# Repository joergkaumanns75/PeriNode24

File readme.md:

# PeriNode24

PeriNode 24 ist ein Zündmodul mit 24 Kanälen und stellt die Standardeinheit dar, welche mehr als einen Zünder pro Kanal auslösen kann.
Ausgelegt ist das Modul für 8 gleichzeitige Zünden mit jeweils 4 in Reihe geschalteten Brückenzündern Typ A.
Wenn nicht alle Kanäle gleichzeitig zünden, kann 6 in Reihe geschaltete Brückenzünder ausgelöst werden, bei guten Bedingungen ggfs. auch mehr.

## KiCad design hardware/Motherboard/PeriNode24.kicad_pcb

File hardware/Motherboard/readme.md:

# PeriNode24 – Motherboard

KiCad-Projekt der PeriNode24-Hauptplatine (ESP32-S3, RFM69HW, 24 Zündkanäle).

| Datei | Inhalt |
|---|---|
| `PeriNode24.kicad_pro` | KiCad-Projekt (hiermit öffnen) |
| `PeriNode24.kicad_sch` | Schaltplan |
| `PeriNode24.kicad_pcb` | Platinenlayout |
| `PeriNode24.pdf` | Schaltplan als PDF |
| `fabrication-toolkit-options.json` | Einstellungen für das Fabrication-Toolkit-Plugin (JLCPCB) |

Verwendet nur KiCad-Standardbibliotheken sowie die Espressif-Bibliothek (Plugin- und Content-Manager).
Lokale Dateien wie `*.kicad_prl`, `fp-info-cache`, Backups und Freerouting-Dateien werden über `hardware/.gitignore` ausgeschlossen.

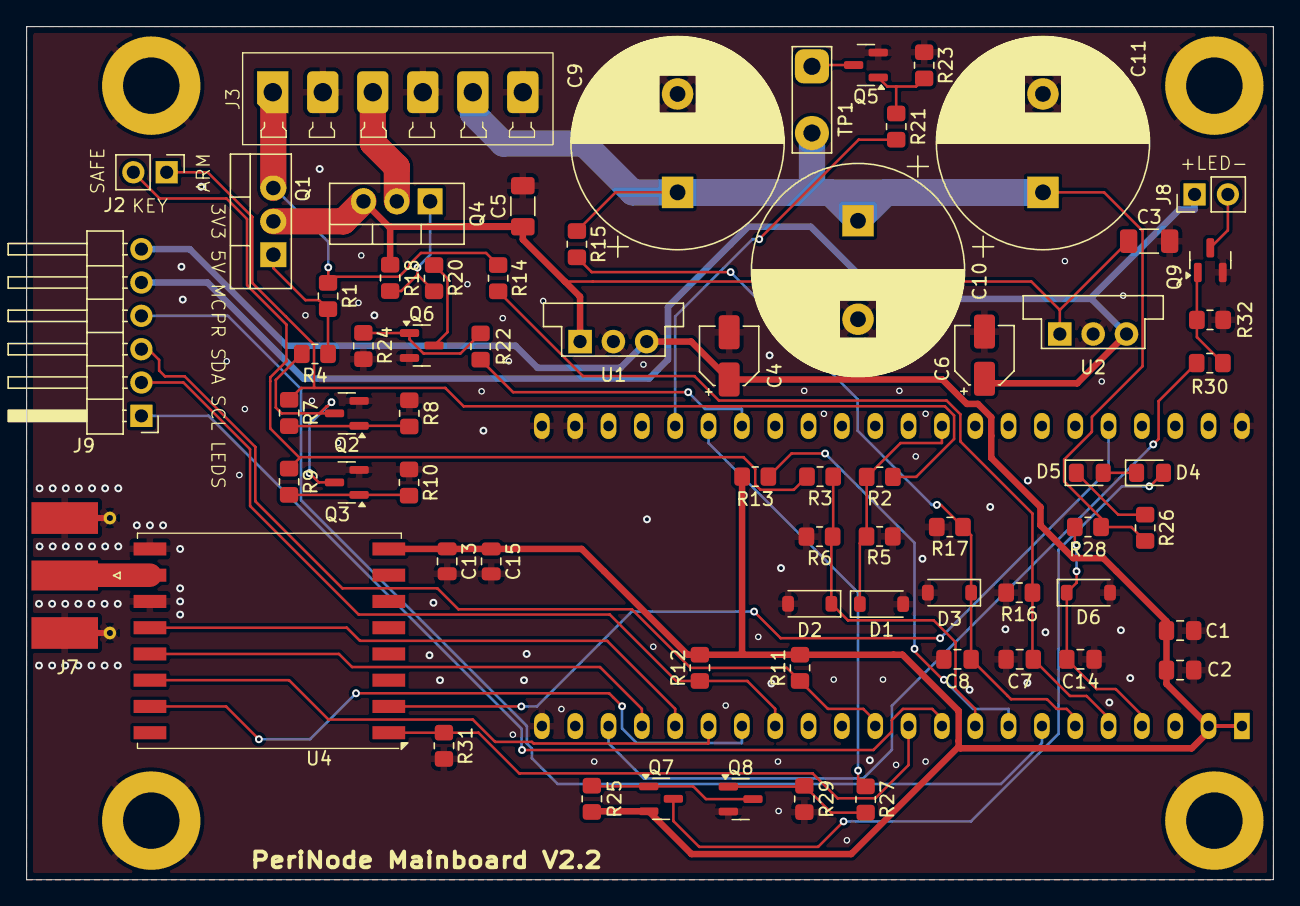
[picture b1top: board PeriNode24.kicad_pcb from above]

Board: 2 copper layers, 95.0 x 65.0 mm, 74 parts (1 on the bottom side), 46 nets.

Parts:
C1, C7, C8, C14: 100n; C_0805_2012Metric_Pad1.18x1.45mm_HandSolder
C2: 22uF/10V; C_0805_2012Metric_Pad1.18x1.45mm_HandSolder
C3, C5: 10uF 50V; C_1206_3216Metric_Pad1.33x1.80mm_HandSolder
C4, C6: 22uF 10V; CP_Elec_4x5.8
C9, C10, C11: 1000uF 63V; CP_Radial_D16.0mm_P7.50mm
C13: 100n; C_0805_2012Metric
C15: 10u; C_0805_2012Metric
D1, D2, D3, D6: 3V3; D_SOD-123
D4, D5: 4148; D_0805_2012Metric_Pad1.15x1.40mm_HandSolder
H1, H2, H3, H4: MTHole; MountingHole_4.3mm_M4_DIN965_Pad
J2: KEYSWITCH; PinHeader_1x02_P2.54mm_Vertical
J3: PowerTerminal; 6 Pin__15EDGVC-3.81
J7: SMA; SMA_Molex_73251-1153_EdgeMount_Horizontal
J8: ARM_LED_OUTPUT; PinHeader_1x02_P2.54mm_Vertical
J9: PowerTerminal; PinHeader_1x06_P2.54mm_Horizontal
Q1, Q4: IRF4905; TO-220-3_Vertical
Q2, Q3, Q6, Q8, Q9: 2N7002K; SOT-23
Q5: NDS 355; SOT-23
Q7: BSS84; SOT-23
R1, R18: 47K; R_0805_2012Metric_Pad1.20x1.40mm_HandSolder
R2, R3: 3K3; R_0805_2012Metric_Pad1.20x1.40mm_HandSolder
R4, R5, R6, R11, R12, R20: 4K7; R_0805_2012Metric_Pad1.20x1.40mm_HandSolder
R7, R8, R9, R10, R13, R23, R24, R25, R28, R29, R31, R32: 10K; R_0805_2012Metric_Pad1.20x1.40mm_HandSolder
R14, R15: 82K; R_0805_2012Metric_Pad1.20x1.40mm_HandSolder
R16: 9K1; R_0805_2012Metric_Pad1.20x1.40mm_HandSolder
R17: 820; R_0805_2012Metric_Pad1.20x1.40mm_HandSolder
R21, R22, R27, R30: 220; R_0805_2012Metric_Pad1.20x1.40mm_HandSolder
R26: 180; R_0805_2012Metric_Pad1.20x1.40mm_HandSolder
TP1: SolderPoint; TestPoint_2Pads_Pitch5.08mm_Drill1.3mm
U1: OKI-78SR-3.3/1.5-W36-C; Converter_DCDC_Murata_OKI-78SR_Vertical
U2: OKI-78SR-5_1.5-W36-C; Converter_DCDC_Murata_OKI-78SR_Vertical
U3: ESP32-S3-DevKitC
U4: RFM69HW; HOPERF_RFM69HW

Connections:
+3.3V: C1.1, C2.1, C4.1, C13.1, C15.1, J9.6, Q7.2 (S), R11.2, R12.2, R13.1, R25.1, U1.3 (OUT), U3.1 (3V3), U3.2 (3V3), U4.8 (3.3V)
+5V: C6.1, J8.1, J9.5, U2.3 (OUT)
+12V: J3.1, Q1.3 (S), R1.1, R14.1
/CHANNEL_LEDS: J9.1, U3.10 (GPIO17/ADC2_CH6)
/Discharge_C_Ign: R21.1, U3.27 (GPIO21)
/ENABLE_WIFI: R13.2, U3.8 (GPIO15/ADC2_CH4/32K_P)
/IN_ARMED_MODE: D1.1 (K), R2.2, R5.1, U3.35 (GPIO38)
/IN_SAFE_MODE: D2.1 (K), R3.2, R6.1, U3.9 (GPIO16/ADC2_CH5/32K_N)
/LED_ARMED: R30.1, U3.20 (GPIO14/ADC2_CH3)
/LED_MINUS: J8.2, Q9.3 (D)
/MCP_RESET: J9.4, U3.7 (GPIO7/ADC1_CH6)
/MISO: U3.19 (GPIO13/ADC2_CH2), U4.13 (MISO)
/MODE_ARMED: R22.1, U3.29 (GPIO48)
/MODE_TEST: R27.1, U3.28 (GPIO47)
/MOSI: U3.17 (GPIO11/ADC2_CH0), U4.14 (MOSI)
/RFM69_INT: U3.40 (GPIO2/ADC1_CH1), U4.2 (DIO0)
/RFM_RESET: R31.1, U3.11 (GPIO18/ADC2_CH7), U4.1 (RESET)
/RF_ANT: J7.1 (In), U4.10 (ANA)
/SCK: U3.18 (GPIO12/ADC2_CH1), U4.12 (SCK)
/SCL: J9.2, R12.1, U3.15 (GPIO9/ADC1_CH8)
/SDA: J9.3, R11.1, U3.12 (GPIO8/ADC1_CH7)
/SS: U3.16 (GPIO10/ADC1_CH9), U4.15 (NSS)
/U_MESS_BATT: C7.2, R14.2, R16.1, U3.5 (GPIO5/ADC1_CH4)
/U_MESS_CHANNEL: C14.1, D6.1 (K), R28.1, U3.4 (GPIO4/ADC1_CH3)
/U_MESS_IGN: C8.2, D3.1 (K), R15.2, R17.1, U3.6 (GPIO6/ADC1_CH5)
/V_EIN: C3.1, C5.1, Q1.2 (D), Q4.3 (S), R18.1, U1.1 (IN), U2.1 (IN)
/V_Stepup: J3.3, Q4.2 (D)
GND: C1.2, C2.2, C3.2, C4.2, C5.2, C6.2, C7.1, C8.1, C9.2, C10.2, C11.2, C13.2, C14.2, C15.2, D1.2 (A), D2.2 (A), D3.2 (A), D6.2 (A), H1.1, H2.1, H3.1, H4.1, J3.2, J3.4, J3.6, J7.2 (Ext), Q2.2 (S), Q3.2 (S), Q5.2 (S), Q6.2 (S), Q8.2 (S), Q9.2 (S), R5.2, R6.2, R8.2, R10.1, R16.2, R17.2, R23.1, R24.1, R29.1, R31.2, R32.1, U1.2 (GND), U2.2 (GND), U3.22 (GND), U3.23 (GND), U3.24 (GND), U3.44 (GND), U4.9 (GND), U4.11 (GND)
unnamed: D4.2 (A), Q7.3 (D)
unnamed: D4.1 (K), D5.2 (A)
unnamed: D5.1 (K), R26.1
unnamed: Q1.1 (G), R1.2, R4.1
unnamed: Q2.3 (D), Q3.3 (D), R4.2
unnamed: Q2.1 (G), R7.2, R8.1
unnamed: Q3.1 (G), R9.2, R10.2
unnamed: Q4.1 (G), R18.2, R20.1
unnamed: Q5.3 (D), TP1.1
unnamed: Q5.1 (G), R21.2, R23.2
unnamed: Q6.3 (D), R20.2
unnamed: Q6.1 (G), R22.2, R24.2
unnamed: Q7.1 (G), Q8.3 (D), R25.2
unnamed: Q8.1 (G), R27.2, R29.2
unnamed: Q9.1 (G), R30.2, R32.2
ON_ARMED_MODE: J2.1, R2.1, R7.1
ON_SAFE_MODE: J2.2, R3.1, R9.1
U_IGN: C9.1, C10.1, C11.1, J3.5, R15.1, R26.2, R28.2, TP1.2
